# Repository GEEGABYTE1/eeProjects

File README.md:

# EE Projects Repo ⚡️

Where I store all my projects related to EE and CE.

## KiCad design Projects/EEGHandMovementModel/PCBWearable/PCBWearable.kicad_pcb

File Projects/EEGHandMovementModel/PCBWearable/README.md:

# PCB Wearable 

PCB wearable designed to read EEG signals. 

Parts Used for Power Management: 
 - Battery Li-Po 3.7V 
 - MCP73831T-2ACI/DT Charging IC 
 - AP2112K-3.3T12G1 3.3V Regulator
 - 3.3V Power Rail

For EEG Acquisition:
 - ADS1299IPAGR EEG Analog Frontend
 - TXBO108PWRG4 Level Translator 

Processing Unit:
 - STM32H743VIT6 MCU 
 - G313-06329-00 Coral Accelerator 

Communication:
 - MDBT5Q0-1MV2 Bluetooth Module
 - G650-04528-01 Antenna

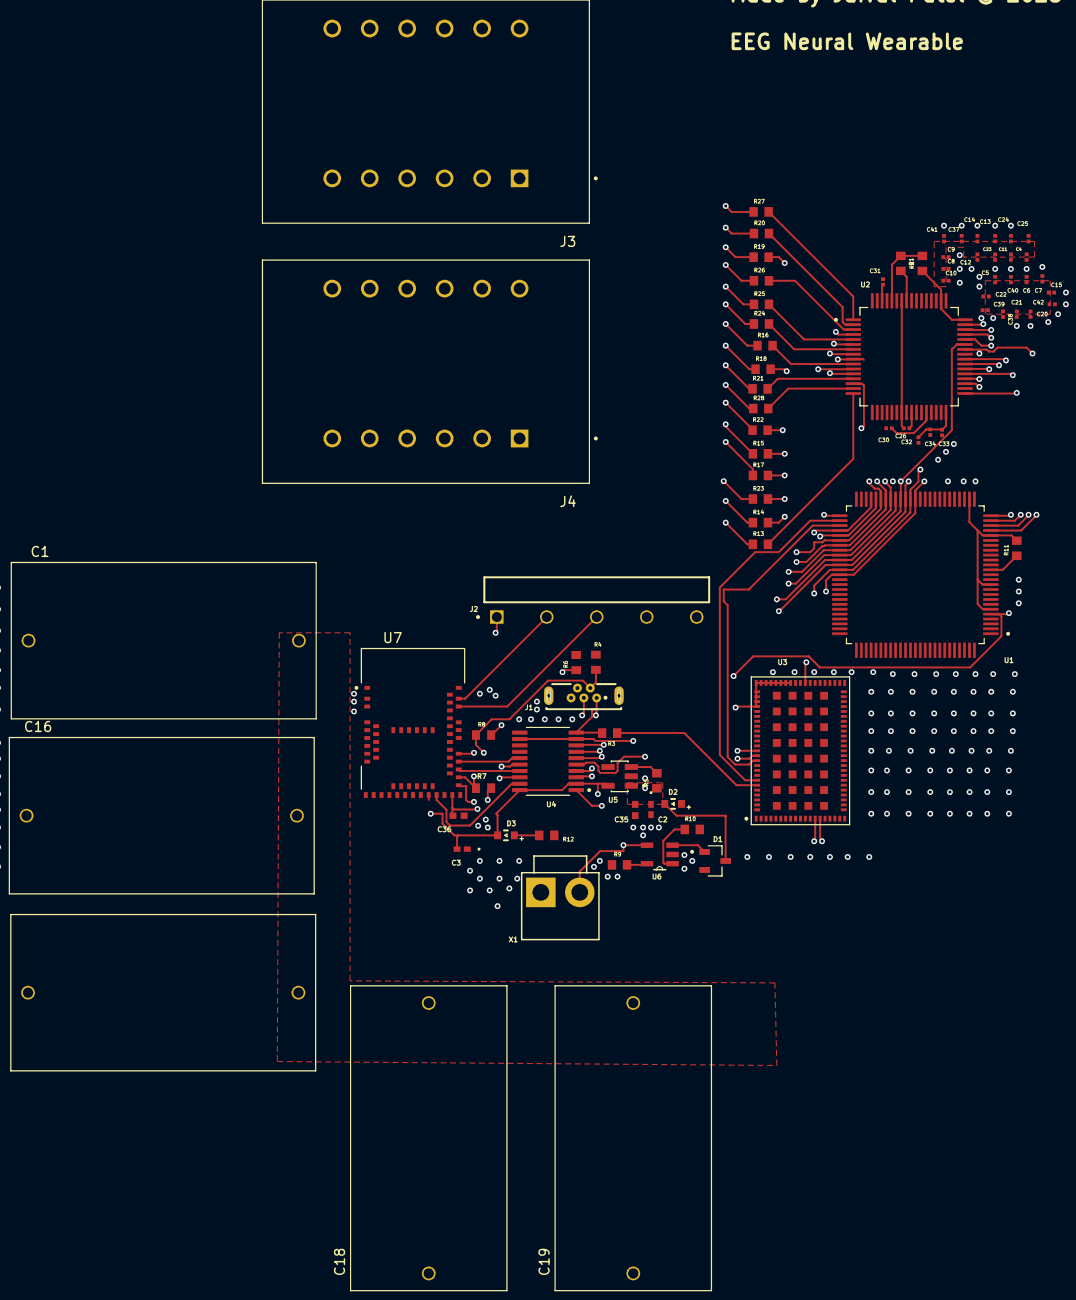
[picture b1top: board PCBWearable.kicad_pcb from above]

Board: 6 copper layers, 82 parts (0 on the bottom side), 83 nets.

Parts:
C1, C16, C17, C18, C19: 10u; CAPRR2750W80L3100T1590H2580
C2, C3: 1u; CAP_GRM155R_MUR
C4, C5, C6, C7, C8, C9, C10, C11, C12, C13, C14, C15, C20, C21, C22, C23, C24, C25, C26, C30, C31, C32, C33, C34, C37, C38, C39, C40, C41, C42: 0.1u; CAPC0603X33N
C35, C36: 4.7u; CAP_GRM15-5_MUR
D1: BAT54-7-F; SOT91P240X110-3N
D2, D3: WL-SMCW_0603_DOME
J1: 614105150621
J2: TSW-205-08-L-S-RA; SAMTEC_TSW-205-08-L-S-RA
J3, J4: 1842801; PHOENIX_1842801
R1, R2, R3, R5, R9, R11: 10k; RESC1508X50N
R4, R6, R7, R8: 22R; RESC1508X55N
R10, R12, R13, R14, R15, R16, R17, R18, R19, R20, R21, R22, R23, R24, R25, R26, R27, R28: 1k; RESC1508X50N
U1: STM32H743VIT6; QFP50P1600X1600X160-100N
U2: ADS1299IPAGR; QFP50P1200X1200X120-64N
U3: G313-06329-00; MODULE_G313-06329-00
U4: TXB0108PWRG4; SOP65P640X120-20N
U5: AP2112K-3.3TRG1; SOT95P285X140-5N
U6: MCP73831T-2ACI_OT; SOT95P280X145-5N
U7: MDBT50Q-1MV2; XCVR_MDBT50Q-1MV2
X1: B2P-VH

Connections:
APSGPIO1: U1.22 (PA0), U2.42 (GPIO1)
APSGPIO2: U1.25 (PA3), U2.44 (GPIO2)
APSGPIO3: U1.24 (PA2), U2.45 (GPIO3)
APSGPIO4: U1.23 (PA1), U2.46 (GPIO4)
BIASREF: R1.1, R2.2, U2.60 (BIASREF)
BLUETOOTH_GPIO0: U1.28 (PA4), U7.47 (P1.00/TRACEDATA0)
BLUETOOTH_GPIO1: U1.29 (PA5), U7.61 (P1.01)
BLUETOOTH_GPIO2: U1.30 (PA6), U7.50 (P1.02)
BLUETOOTH_GPIO3: U1.31 (PA7), U7.60 (P1.03)
BLUETOOTH_GPIO4: U1.67 (PA8), U7.56 (P1.04)
CLK: U1.5 (PE6), U2.37 (CLK), U4.5 (A4)
CLKREQ_L: U1.53 (PB14), U3.78 (CLKREQ_L)
CS: U1.42 (PE12), U1.59 (PD12), U2.39 (~CS), U4.6 (A5), U4.15 (B5), U7.39 (P0.15)
DIN: U1.40 (PE10), U1.61 (PD14), U2.34 (DIN), U2.DIN (DGND), U4.4 (A3), U4.17 (B3), U7.37 (P0.13)
DOUT: U1.41 (PE11), U1.DOUT (PD13), U2.43 (DOUT), U4.3 (A2), U4.18 (B2), U7.36 (P0.14), U7.41 (P0.17)
DRDY: U1.38 (PE8), U1.63 (PC6), U2.47 (~DRDY), U4.1 (A1), U4.19 (VCCB), U7.22 (P0.06), U7.30 (VDDH)
GND: C1.1, C2.2, C3.1, C4.2, C5.2, C6.2, C7.2, C8.2, C9.2, C10.2, C11.2, C12.2, C13.2, C14.2, C15.2, C16.1, C17.1, C18.1, C19.1, C20.2, C21.2, C22.2, C23.2, C24.2, C25.2, C30.2, C31.2, C32.2, C33.2, C34.2, C35.2, C36.2, C37.2, C38.2, C39.2, C40.2, C41.2, C42.2, J1.5 (GND), J2.05, R9.1, U1.10 (VSS), U1.19 (VSSA), U1.26 (VSS__1), U1.49 (VSS__2), U1.74 (VSS__3), U1.99 (VSS__4), U2.49 (DGND__1), U2.51 (DGND__2), U2.52 (CLKSEL), U2.DIN (DAISY_IN), U3.1 (GND), U3.2 (GND), U3.3 (GND), U3.6 (GND), U3.9 (GND), U3.12 (GND), U3.15 (GND), U3.16 (GND), U3.17 (GND), U3.18 (GND), U3.19 (GND), U3.20 (GND), U3.21 (GND), U3.22 (GND), U3.23 (GND), U3.24 (GND), U3.25 (GND), U3.26 (GND), U3.27 (GND), U3.28 (GND), U3.29 (GND), U3.30 (GND), U3.31 (GND), U3.32 (GND), U3.33 (GND), U3.34 (GND), U3.35 (GND), U3.36 (GND), U3.38 (GND), U3.39 (GND), U3.40 (GND), U3.41 (GND), U3.42 (GND), U3.43 (GND), U3.44 (GND), U3.45 (GND), U3.46 (GND), U3.47 (GND), U3.48 (GND), U3.51 (GND), U3.55 (GND), U3.68 (GND), U3.69 (GND), U3.70 (GND), U3.71 (GND), U3.72 (GND), U3.73 (GND), U3.74 (GND), U3.75 (GND), U3.79 (GND), U3.80 (GND), U3.81 (GND), U3.86 (GND), U3.87 (GND), U3.88 (GND), U3.89 (GND), U3.90 (GND), U3.91 (GND), U3.92 (GND), U3.93 (GND), U3.94 (GND), U3.95 (GND), U3.96 (GND), U3.97 (GND), U3.98 (GND), U3.99 (GND), U3.100 (GND), U3.101 (GND), U3.102 (GND), U3.103 (GND), U3.104 (GND), U3.105 (GND), U3.106 (GND), U3.107 (GND), U3.108 (GND), U3.109 (GND), U3.110 (GND), U3.111 (GND), U3.112 (GND), U3.113 (GND), U3.114 (GND), U3.115 (GND), U3.116 (GND), U3.117 (GND), U3.118 (GND), U3.119 (GND), U3.120 (GND), U4.11 (GND), U5.2 (GND), U6.2 (VSS), U7.1 (GND), U7.2 (GND), U7.15 (GND), U7.33 (GND), U7.55 (GND), X1.1
IN1N: J4.01, R28.1
IN1P: J3.01, R13.1
IN2N: J4.02, R21.1
IN2P: J3.02, R14.1
IN3N: J4.03, R22.1
IN3P: J3.03, R15.1
IN4N: J4.04, R23.1
IN4P: J3.04, R16.1
IN5N: J4.05, R24.1
IN5P: J3.05, R17.1
IN6N: J4.06, R25.1
IN6P: J3.06, R18.1
IN7N: J4.07, R26.1
IN7P: J3.07, R19.1
IN8N: J4.08, R27.1
IN8P: J3.08, R20.1
INTR: U1.46 (PB10), U1.55 (PD8), U3.77 (INTR)
unnamed: D2.2, R10.2
unnamed: D3.2, R12.2
unnamed: J1.S1, J1.S2
unnamed: R11.1, U1.14 (NRST)
unnamed: R4.2, U1.70 (PA11)
unnamed: R6.2, U1.71 (PA12)
unnamed: R12.1, U1.81 (PD0)
unnamed: C31.1, U2.62 (BIASIN)
unnamed: R28.2, U2.15 (IN1N)
unnamed: R13.2, U2.16 (IN1P)
unnamed: R21.2, U2.13 (IN2N)
unnamed: R14.2, U2.14 (IN2P)
unnamed: R22.2, U2.11 (IN3N)
unnamed: R15.2, U2.12 (IN3P)
unnamed: R23.2, U2.9 (IN4N)
unnamed: R16.2, U2.10 (IN4P)
unnamed: R24.2, U2.7 (IN5N)
unnamed: R17.2, U2.8 (IN5P)
unnamed: R25.2, U2.5 (IN6N)
unnamed: R18.2, U2.6 (IN6P)
unnamed: R26.2, U2.3 (IN7N)
unnamed: R19.2, U2.4 (IN7P)
unnamed: R27.2, U2.1 (IN8N)
unnamed: R20.2, U2.2 (IN8P)
unnamed: C30.1, U2.28 (VCAP1), U2.30 (VCAP2)
unnamed: U2.26 (VCAP4), U2.55 (VCAP3)
unnamed: C26.2, U2.25 (VREFN)
unnamed: R8.2, U3.14 (USB2_D_N)
unnamed: R7.2, U3.13 (USB2_D_P)
unnamed: R3.1, U3.83 (USB_SEL)
unnamed: R5.2, U5.3 (EN)
unnamed: R9.2, U6.5 (PROG)
unnamed: R10.1, U6.1 (STAT)
unnamed: D1.1, U6.3 (VBAT)
PMIC_EN: U1.51 (PB12), U3.53 (PMIC_EN)
POWERRAIL_OUT: C1.2, C3.2, C4.1, C5.1, C6.1, C7.1, C8.1, C9.1, C10.1, C11.1, C12.1, C13.1, C14.1, C15.1, C16.2, C17.2, C18.2, C19.2, C20.1, C21.1, C22.1, C23.1, C24.1, C25.1, C37.1, C38.1, C39.1, C40.1, C41.1, C42.1, D3.1, J2.01, R2.1, R11.2, U1.6 (VBAT), U1.11 (VDD), U1.21 (VDDA), U1.27 (VDD__1), U1.50 (VDD__2), U1.75 (VDD__3), U1.100 (VDD__4), U2.19 (AVDD@1), U2.21 (AVDD@1__1), U2.22 (AVDD@1__2), U2.48 (DVDD), U2.50 (DVDD__1), U2.54 (AVDD1), U2.56 (AVDD@1__3), U2.59 (AVDD@2), U3.54 (AON), U3.56 (VIN), U3.57 (VIN), U3.58 (VIN), U3.59 (VIN), U3.60 (VIN), U3.61 (VIN), U3.62 (VIN), U3.63 (VIN), U3.64 (VIN), U3.65 (VIN), U3.66 (VIN), U3.67 (VIN), U4.2 (VCCA), U4.20 (B1), U5.5 (VOUT), U7.28 (VDD)
PWDN: U1.45 (PE15), U1.PWDN (PD9), U2.35 (~PWDN), U4.9 (A8), U4.12 (B8)
RESET: U1.44 (PE14), U1.57 (PD10), U2.36 (~RESET), U4.7 (A6), U4.14 (B6)
RST_L: U1.47 (PB11), U1.54 (PB15), U3.76 (RST_L), U7.40 (P0.18/~RESET)
SCLK: U1.39 (PE9), U1.62 (PD15), U2.40 (SCLK), U4.16 (B4), U7.24 (P0.08)
SD_ALARM: U1.52 (PB13), U3.82 (SD_ALARM)
START: U1.43 (PE13), U1.58 (PD11), U2.38 (START), U4.8 (A7), U4.13 (B7)
SWDCLK_BLUETOOTH: J2.02, U7.53 (SWDCLK)
SWDIO_BLUETOOTH: J2.03, U7.51 (SWDIO)
USB_DN: J1.2 (D-), R4.1, R8.1, U7.34 (D-)
USB_DP: J1.3 (D+), R6.1, R7.1, U7.35 (D+)
VBATT_IN: C36.1, J1.1 (VBUS), R3.2, U4.10 (OE), U6.4 (VDD), U7.32 (VBUS), X1.2
VBAT_OUT: C2.1, C35.1, D1.3, D2.1, R5.1, U5.1 (VIN)
VREFF: C26.1, C32.1, C33.1, C34.1, R1.2, U2.20 (AVSS@1), U2.23 (AVSS@1__1), U2.24 (VREFP), U2.32 (AVSS@1__2), U2.53 (AVSS1), U2.57 (AVSS@1__3), U2.58 (AVSS@2)

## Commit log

2025-03-18 documentation
2025-03-19 initial neural net
2025-03-21 improved neural net
2025-03-22 visualization for training loss
2025-03-22 dataset handling
2025-03-22 utils, dataset, neuralnet
2025-03-22 readme
2025-03-22 bugs
2025-03-24 cleanup
2025-03-24 working on improved alexnet C implementation
2025-03-24 currently 6 s slower
2025-03-24 achieved 0.01% performance boost
2025-03-27 achieved 3x speed max
2025-03-28 readme leading to technical doc
2025-05-26 trackSim Project
2025-05-26 file change
2025-06-16 new project
2025-06-20 transformer bci encoder
